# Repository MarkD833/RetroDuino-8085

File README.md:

# RetroDuino-8085

I've been toying with the idea of creating an 8085 based microprocessor board around the size of an Arduino UNO ever since I came across the [65uino](https://hackaday.io/project/190260-65uino) board on the hackaday website.

# Table of contents
* [The wish list](#the-basics-of-the-design)
  - [The Microprocessor](#the-microprocessor)
  - [ROM](#rom)
  - [RAM](#ram)
  - [Serial](#serial)
  - [I/O](#digital-input-output)
  - [ADC](#analogue-to-digital-converter)
* [Board Layout](#the-board-layout)
* [Assembly Instructions](#assembly-instructions)
* [The 16V8 GAL](#the-16v8-gal)
* [Pinout](#pinout)
* [Software](#software)
* [PCB Files](#the-board-design-files)
* [Known Errors](#known-errors)
* [History](#history)
## The basics of the design

I started off with some basics:
| Item | Notes |
| :---- | :---- |
| Microprocessor | an 8085 device but which one and what clock speed |
| ROM | At least 8K maybe 16K - but do I need that much?  |
| RAM | 32K would be good to aim for |
| Serial | 1 serial port but bit bang or hardware? |
| I/O | Bit programmable i/o |
| Analogue In | A multi channel ADC if there's room |
| LEDs | At least 1 user LED |

Oh, and one other requirement - no surface mount chips or hard to solder parts!

That's quite a lot to cram into the footprint on an Arduino UNO!

After a lot of playing around with an Arduino UNO prototyping board and various chip sockets I came up with a basic design and layout.

## The Microprocessor

The 8085 is mostly seen in a 40-pin DIL package. That's a huge amount of real estate on a footprint the size of an Arduino UNO. I discovered that OKI Semiconductor manufactured an 80C85 in a 44-pin PLCC package (MSM80C85AHGS-2K). After a quick bit of digging I located the datasheet and also a source on ebay that was selling some of the chips as NOS (New Old Stock).

Additional board space is consumed as the 8085 has a multiplexed address and data bus. The lower 8-bits are shared between D0..D7 and A0..A7 and an 8-bit latch (74LS573) is used to capture A0..A7.

Another design challenge is that the 8085 interrupts (if I were to use them) are active high rather than active low! 

The 8085 is clocked from an 11.0592MHz crystal, which gives an actual clock of 5.5296MHz (the 8085 divides the crystal frequency by 2). I've yet to experiment to see the effects of a higher frequency even though I'm exceeding the manufacturers 10MHz clock by 10% already.

## ROM

There are quite a few ROM devices available in a PLCC package as well, but I decided to go with a Winbond W27C512 64K x 8 EEPROM in a 28-pin DIL package. There's plenty for sale on ebay too. The reason for going the DIL package route will become clear with the choice of RAM device.

## RAM

I couldn't find any suitable RAM devices in PLCC format so the project success was looking rather bleak. Then I discovered that there were some SRAM devices available in DIL packages that were only 0.3in wide (called Skinny-DIP if I recall correctly). I then got lucky and sourced some UMC UM61512AK 64K x 8 SRAMs in a skinny 32-pin DIL package.

The RAM chip could sit underneath the ROM chip and I would save a lot of board space.

## Serial

I thought about bit banging the serial port using the SID and SOD pins of the 8085 but decided to try and go with real hardware. Again board space was at a premium so the hunt was on for a small UART device. A lot of serial chips have a large number of pins dedicated to various handshaking signals as well as synchronous data transfer - although some devices allow repurposing of these signals as discrete inputs or outputs. They are all still quite large chips in either PLCC or 0.6in DIL packages.

I then discovered a Philips SCC2691 UART (SCC2691AC1N24) that was available in a 0.3in wide 24-pin DIL package. It had an internal baud rate generator and a single 16-bit timer/counter as well. 

## Digital Input Output

I really wanted the I/O chip to have pin programmable direction control. That ruled out the 8155 and 8255 chips. It took a lot of searching but I then discovered a Zilog Z85C36. It had 2x 8-bit bit programmable I/O ports as well as 3x 16-bit timer/counters. That would be perfect!

Except that it wasn't! In my v1.0 design, I couldn't get the Z85C36 to respond at all. I don't know quite what the issue was as I was sure that I was meeting the timing requirements - but clearly something wasn't right.

In order to salvage the situation, I changed the I/O chip to a WDC W65C22S device. The chip still gave me 2x 8-bit bit programmable I/O ports, but only 2x 16-bit timer/counters.

## Analogue to Digital Converter

If I could fit it in, then an a National Semiconductor ADC0844 might work out - it's a 4 channel ADC in a 20-pin DIL package. 

# The board layout

There was quite a bit of massaging to get everything to fit as I also used a GAL16V8 to handle address decoding and interrupt inversion. The result was a board slightly longer than an Arduino UNO (but the same width).

This is an annotated 3D view of the board generated by Kicad as it stands at v1.2.

The thick white lines on the silkscreen just to the right of the FTDI serial port connector and the ADC0844 chip show the outline of an actual Arduino UNO board.

# Assembly Instructions

Assembly of the board is pretty straightforward with a few things of note.

1. Solder all the small SMD resistors and capacitors first - especially on the top of the board as there is very little room once the IC sockets are fitted.
2. Solder the microprocessor crystal and Reset device before fitting the 44-pin PLCC sockets otherwise you may find that the crystal will not fit down between the 44-pin PLCC sockets. 
3. Depending on the particular DIL socket(s) used for the SCC2691 UART, you may need to remove some of the plastic from the socket so that the 3.6864MHz crystal fits. I used 2 turned-pin sockets, an 8-pin and a 16-pin, to create the 24-pin socket needed. I found that the turned pin socket was less bulky than a regular socket.
4. The 28-pin DIL socket for the W27C512 ROM needs modifying. As the RAM chip will be sitting underneath the ROM chip, I removed the 3 pieces of plastic between the 2 rows of pins - effectively creating two separate 14-pin SIL sockets.
5. Lastly, solder the 4 SIL sockets. These pretty much seal off the top of the board for any further access with a soldering iron, so make sure that the board works before fitting thse. 

This is a photo of the RetroDuino-8085 board showing the location of the 3.6864MHz UART crystal and the modified 28-pin DIL socket.

# The 16V8 GAL

There's so little space on this board that a GAL seemed the logical choice to handle the usual discrete logic. The GAL does address and i/o decoding as follows:
* Memory space
  * 0x0000 - 0x3FFF selects the ROM
  * 0x4000 - 0xFFFF selets the RAM
* I/O space
  * 0x00 - 0x3F selects the SCC2692 UART
  * 0x40 - 0x7F selects the W65C22S digital i/o chip
  * 0x80 - 0xBF selects the ADC0844 ADC chip
 
In addition, the GAL inverts the SCC2692 and W65C22S interrupt signals.

Finally, the GAL has the ability to completely switch out the ROM to give access to the full 64K or RAM. The 8085 SOD pin is used to control this feature.

The GAL files are in the code folder.

# Pinout
Below is an image of the pinout I'm using - laid out in a similar way to the Arduino pinout diagrams found on the web. Note that the I2C and SPI signals will hopefully be generated by a software implementation of a hardware interface. 

# Software

Please see the readme in the Code folder for more details on the software.

# The board design files

The board folder holds the gerber files that were sent to JLCPCB to make the board. It's a 4 layer board but small enough to get it made very cheaply.

The design was done using Kicad 7.0. I'm not sure exactly which files I need to share for the schematic and board layout so I've put the .kicad_pro, .kicad_sch & .kicad_sch files into the board folder. There's also the BOM as a CSV file showing the components used.

# Known errors

Yep, there are errors with v1.2. So far:
* LED D2 wrong way round
* LED D3 wrong way round

# History
* v1.2
  * Used ALE to clock the GAL rather than SYSCLK.
  * Removed the CompactFlash socket and associated passives.
  * Used 8085 SOD discrete to switch out the ROM.
  * Addition of 2nd user LED.
  * Repositioning of the FTDI connector.
* v1.1 
  * Updated design using the W65C22 PIA chip.
* v1.0
  * Initial design using the Z85C36 CIO chip.

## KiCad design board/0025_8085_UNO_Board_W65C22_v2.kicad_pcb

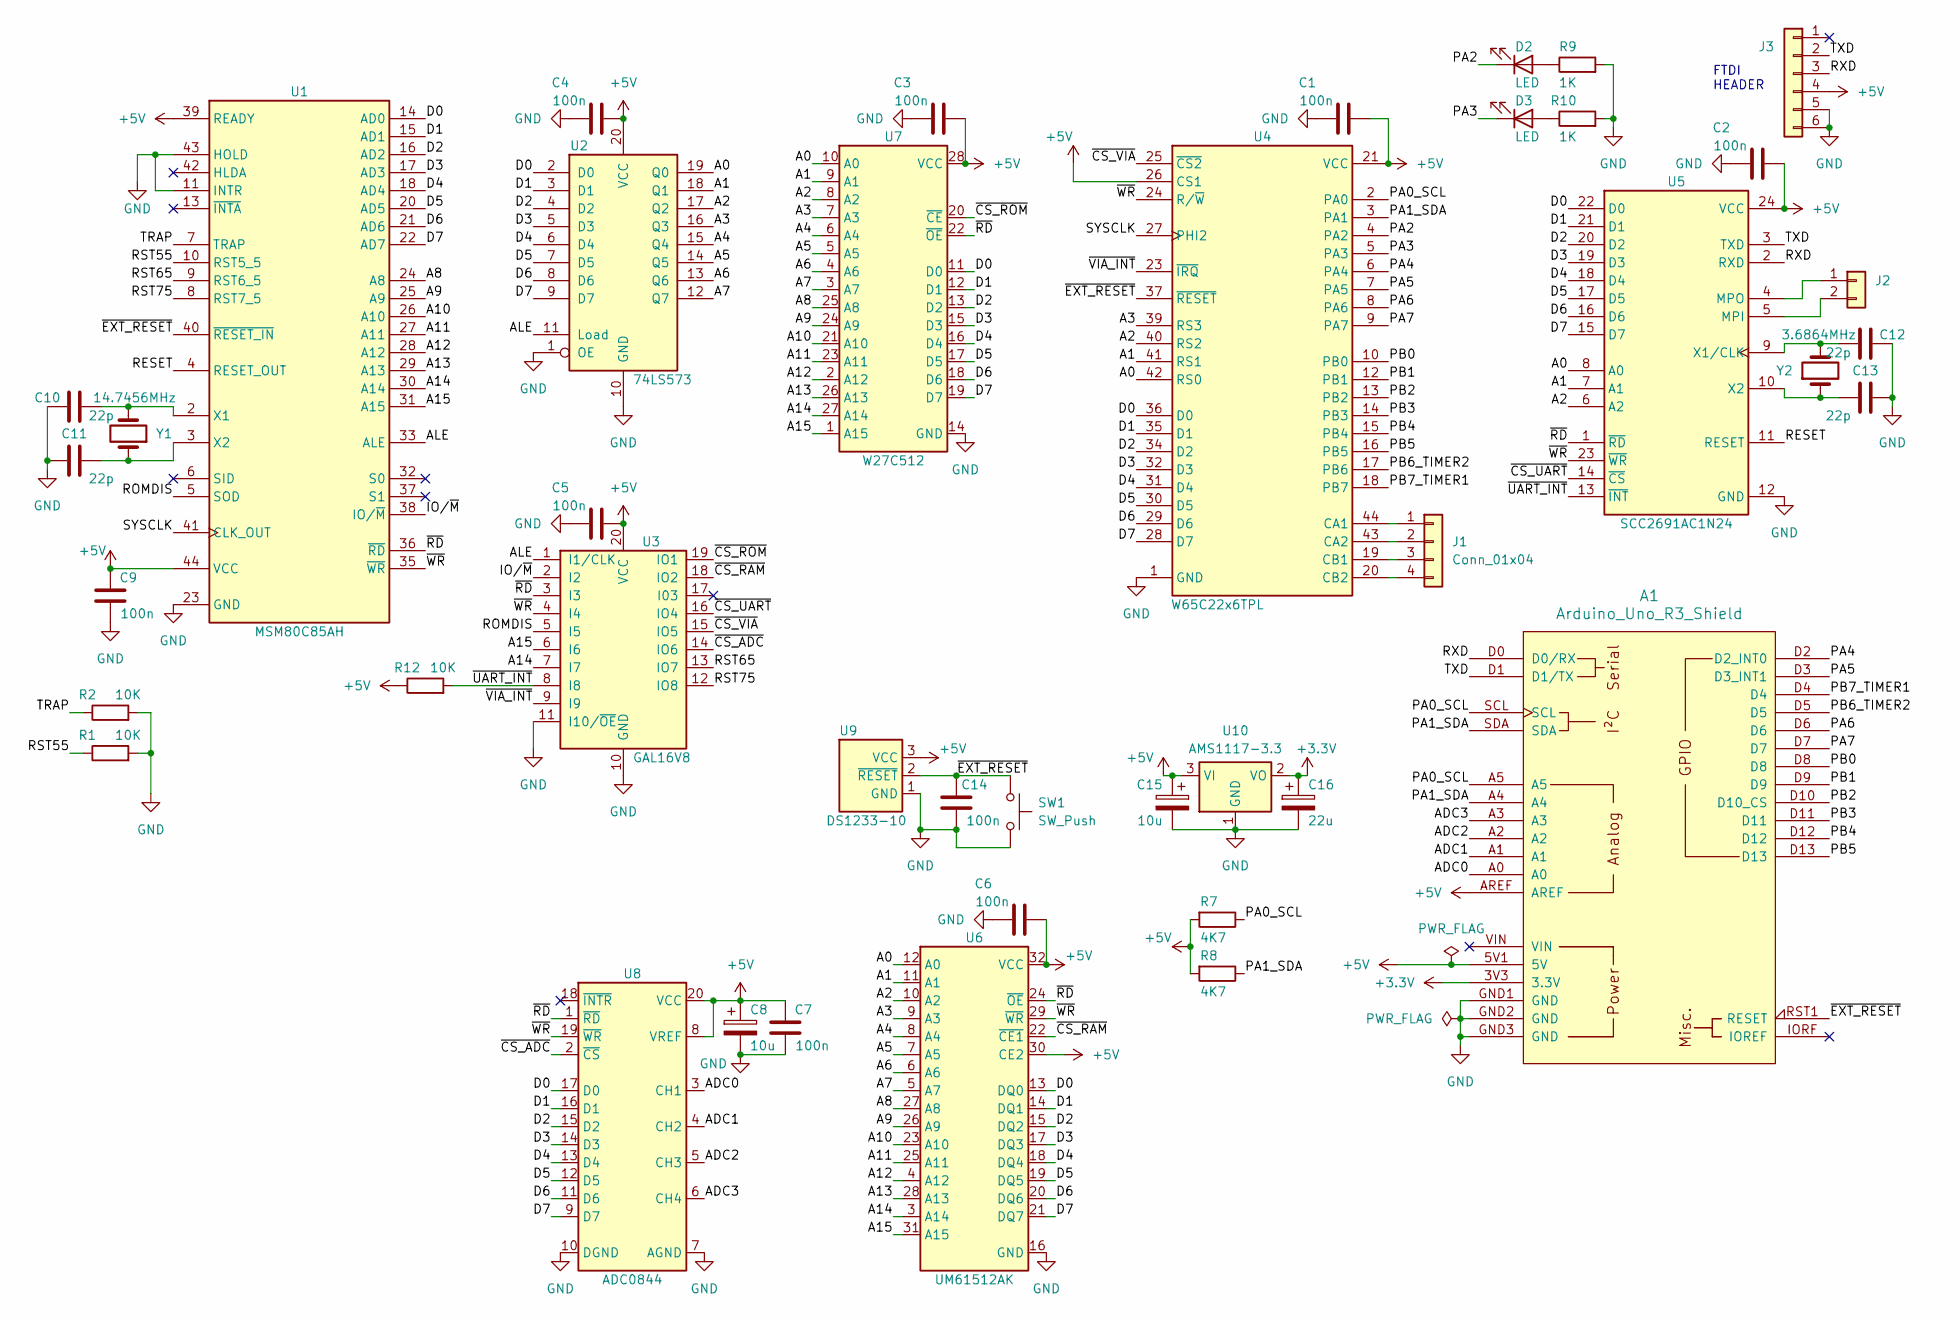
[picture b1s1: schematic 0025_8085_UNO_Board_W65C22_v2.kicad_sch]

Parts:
A1: Arduino_Uno_R3_Shield; Arduino_Uno_8085_Base_1
C1, C2, C3, C4, C5, C6, C7, C9, C14: 100n; C_0603_1608Metric_Pad1.08x0.95mm_HandSolder
C8: 10u; CP_EIA-3216-18_Kemet-A
C10, C11, C12, C13: 22p; C_0603_1608Metric_Pad1.08x0.95mm_HandSolder
C15: 10u; CP_EIA-3216-18_Kemet-A_Pad1.58x1.35mm_HandSolder
C16: 22u; CP_EIA-6032-28_Kemet-C
D2, D3: LED; LED_0805_2012Metric_Pad1.15x1.40mm_HandSolder
J1: Conn_01x04; PinHeader_1x04_P2.54mm_Vertical
J2: PinHeader_1x02_P2.54mm_Vertical
J3: PinHeader_1x06_P2.54mm_Vertical
R1, R2, R12: 10K; R_0805_2012Metric_Pad1.20x1.40mm_HandSolder
R7, R8: 4K7; R_0805_2012Metric_Pad1.20x1.40mm_HandSolder
R9, R10: 1K; R_0805_2012Metric_Pad1.20x1.40mm_HandSolder
SW1: SW_Push; TACTILE_SWITCH_SMD_6.0X3.5MM
U1: MSM80C85AH; PLCC-44_THT-Socket
U2: 74LS573; DIP-20_W7.62mm
U3: GAL16V8; DIP-20_W7.62mm
U4: W65C22x6TPL; PLCC-44_THT-Socket
U5: SCC2691AC1N24; DIP-24_W7.62mm
U6: UM61512AK; DIP-32_W7.62mm
U7: W27C512; DIP-28_W15.24mm
U8: ADC0844; DIP-20_W7.62mm
U9: DS1233-10; TO-92L_Inline
U10: AMS1117-3.3; SOT-223-3_TabPin2
Y1: 14.7456MHz; Crystal_HC49-U_Vertical
Y2: 3.6864MHz; Crystal_HC49-U_Vertical

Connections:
+3.3V: A1.3V3 (3.3V), C16.1, U10.2 (VO)
+5V: A1.5V1 (5V), A1.AREF, C1.2, C2.2, C3.2, C4.2, C5.2, C6.2, C7.1, C8.1, C9.1, C15.1, J3.4, R7.2, R8.2, R12.1, U1.39 (READY), U1.44 (VCC), U2.20 (VCC), U3.20 (VCC), U4.21 (VCC), U4.26 (CS1), U5.24 (VCC), U6.30 (CE2), U6.32 (VCC), U7.28 (VCC), U8.8 (VREF), U8.20 (VCC), U9.3 (VCC), U10.3 (VI)
/A0: U2.19 (Q0), U4.42 (RS0), U5.8 (A0), U6.12 (A0), U7.10 (A0)
/A1: U2.18 (Q1), U4.41 (RS1), U5.7 (A1), U6.11 (A1), U7.9 (A1)
/A2: U2.17 (Q2), U4.40 (RS2), U5.6 (A2), U6.10 (A2), U7.8 (A2)
/A3: U2.16 (Q3), U4.39 (RS3), U6.9 (A3), U7.7 (A3)
/A4: U2.15 (Q4), U6.8 (A4), U7.6 (A4)
/A5: U2.14 (Q5), U6.7 (A5), U7.5 (A5)
/A6: U2.13 (Q6), U6.6 (A6), U7.4 (A6)
/A7: U2.12 (Q7), U6.5 (A7), U7.3 (A7)
/A8: U1.24 (A8), U6.27 (A8), U7.25 (A8)
/A9: U1.25 (A9), U6.26 (A9), U7.24 (A9)
/A10: U1.26 (A10), U6.23 (A10), U7.21 (A10)
/A11: U1.27 (A11), U6.25 (A11), U7.23 (A11)
/A12: U1.28 (A12), U6.4 (A12), U7.2 (A12)
/A13: U1.29 (A13), U6.28 (A13), U7.26 (A13)
/A14: U1.30 (A14), U3.7 (I7), U6.3 (A14), U7.27 (A14)
/A15: U1.31 (A15), U3.6 (I6), U6.31 (A15), U7.1 (A15)
/ADC0: A1.A0, U8.3 (CH1)
/ADC1: A1.A1, U8.4 (CH2)
/ADC2: A1.A2, U8.5 (CH3)
/ADC3: A1.A3, U8.6 (CH4)
/ALE: U1.33 (ALE), U2.11 (Load), U3.1 (I1/CLK)
/D0: U1.14 (AD0), U2.2 (D0), U4.36 (D0), U5.22 (D0), U6.13 (DQ0), U7.11 (D0), U8.17 (D0)
/D1: U1.15 (AD1), U2.3 (D1), U4.35 (D1), U5.21 (D1), U6.14 (DQ1), U7.12 (D1), U8.16 (D1)
/D2: U1.16 (AD2), U2.4 (D2), U4.34 (D2), U5.20 (D2), U6.15 (DQ2), U7.13 (D2), U8.15 (D2)
/D3: U1.17 (AD3), U2.5 (D3), U4.32 (D3), U5.19 (D3), U6.17 (DQ3), U7.15 (D3), U8.14 (D3)
/D4: U1.18 (AD4), U2.6 (D4), U4.31 (D4), U5.18 (D4), U6.18 (DQ4), U7.16 (D4), U8.13 (D4)
/D5: U1.20 (AD5), U2.7 (D5), U4.30 (D5), U5.17 (D5), U6.19 (DQ5), U7.17 (D5), U8.12 (D5)
/D6: U1.21 (AD6), U2.8 (D6), U4.29 (D6), U5.16 (D6), U6.20 (DQ6), U7.18 (D6), U8.11 (D6)
/D7: U1.22 (AD7), U2.9 (D7), U4.28 (D7), U5.15 (D7), U6.21 (DQ7), U7.19 (D7), U8.9 (D7)
/IO/~M: U1.38 (IO/~M), U3.2 (I2)
/PA0_SCL: A1.A5, A1.SCL, R7.1, U4.2 (PA0)
/PA1_SDA: A1.A4, A1.SDA, R8.1, U4.3 (PA1)
/PA2: D2.1 (K), U4.4 (PA2)
/PA3: D3.1 (K), U4.5 (PA3)
/PA4: A1.D2 (D2_INT0), U4.6 (PA4)
/PA5: A1.D3 (D3_INT1), U4.7 (PA5)
/PA6: A1.D6, U4.8 (PA6)
/PA7: A1.D7, U4.9 (PA7)
/PB0: A1.D8, U4.10 (PB0)
/PB1: A1.D9, U4.12 (PB1)
/PB2: A1.D10 (D10_CS), U4.13 (PB2)
/PB3: A1.D11, U4.14 (PB3)
/PB4: A1.D12, U4.15 (PB4)
/PB5: A1.D13, U4.16 (PB5)
/PB6_TIMER2: A1.D5, U4.17 (PB6)
/PB7_TIMER1: A1.D4, U4.18 (PB7)
/RESET: U1.4 (RESET_OUT), U5.11 (RESET)
/ROMDIS: U1.5 (SOD), U3.5 (I5)
/RST55: R1.1, U1.10 (RST5_5)
/RST65: U1.9 (RST6_5), U3.13 (IO7)
/RST75: U1.8 (RST7_5), U3.12 (IO8)
/RXD: A1.D0 (D0/RX), J3.3, U5.2 (RXD)
/SYSCLK: U1.41 (CLK_OUT), U4.27 (PHI2)
/TRAP: R2.1, U1.7 (TRAP)
/TXD: A1.D1 (D1/TX), J3.2, U5.3 (TXD)
/~CS_ADC: U3.14 (IO6), U8.2 (~CS)
/~CS_RAM: U3.18 (IO2), U6.22 (~CE1)
/~CS_ROM: U3.19 (IO1), U7.20 (~CE)
/~CS_UART: U3.16 (IO4), U5.14 (~CS)
/~CS_VIA: U3.15 (IO5), U4.25 (~CS2)
/~EXT_RESET: A1.RST1 (RESET), C14.1, SW1.1, U1.40 (~RESET_IN), U4.37 (~RESET), U9.2 (~RESET)
/~RD: U1.36 (~RD), U3.3 (I3), U5.1 (~RD), U6.24 (~OE), U7.22 (~OE), U8.1 (~RD)
/~UART_INT: R12.2, U3.8 (I8), U5.13 (~INT)
/~VIA_INT: U3.9 (I9), U4.23 (~IRQ)
/~WR: U1.35 (~WR), U3.4 (I4), U4.24 (R/~W), U5.23 (~WR), U6.29 (~WR), U8.19 (~WR)
GND: A1.GND1 (GND), A1.GND2 (GND), A1.GND3 (GND), C1.1, C2.1, C3.1, C4.1, C5.1, C6.1, C7.2, C8.2, C9.2, C10.1, C11.2, C12.1, C13.2, C14.2, C15.2, C16.2, J3.5, J3.6, R1.2, R2.2, R9.2, R10.2, SW1.2, U1.11 (INTR), U1.23 (GND), U1.43 (HOLD), U2.1 (OE), U2.10 (GND), U3.10 (GND), U3.11 (I10/~OE), U4.1 (GND), U5.12 (GND), U6.16 (GND), U7.14 (GND), U8.7 (AGND), U8.10 (DGND), U9.1 (GND), U10.1 (GND)
unnamed: D2.2 (A), R9.1
unnamed: D3.2 (A), R10.1
unnamed: J1.1, U4.44 (CA1)
unnamed: J1.2, U4.43 (CA2)
unnamed: J1.3, U4.19 (CB1)
unnamed: J1.4, U4.20 (CB2)
unnamed: J2.1, U5.4 (MPO)
unnamed: J2.2, U5.5 (MPI)
unnamed: C10.2, U1.2 (X1), Y1.2
unnamed: C11.1, U1.3 (X2), Y1.1
unnamed: C12.2, U5.9 (X1/CLK), Y2.2
unnamed: C13.1, U5.10 (X2), Y2.1

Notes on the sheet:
FTDI HEADER

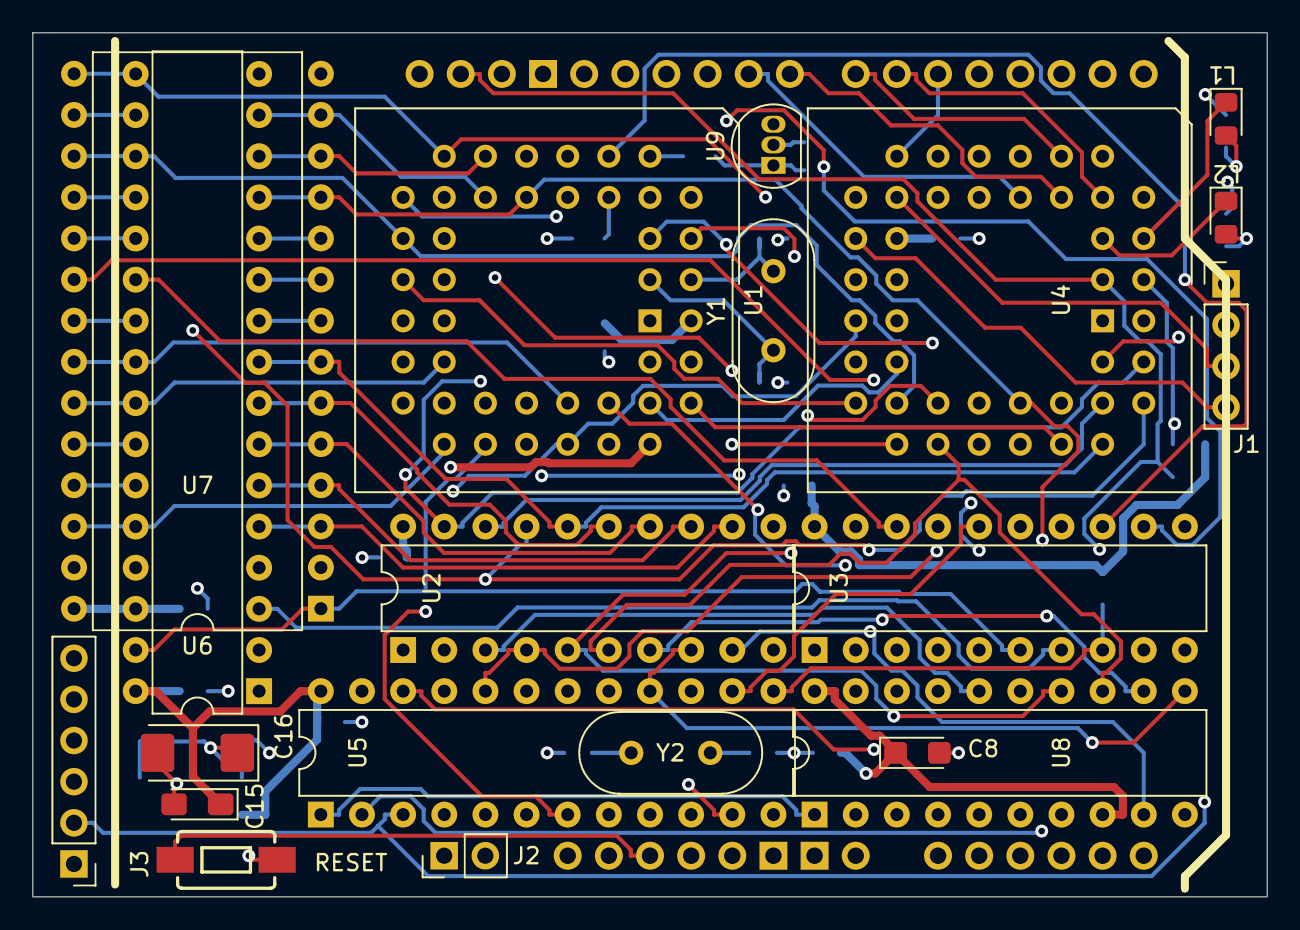
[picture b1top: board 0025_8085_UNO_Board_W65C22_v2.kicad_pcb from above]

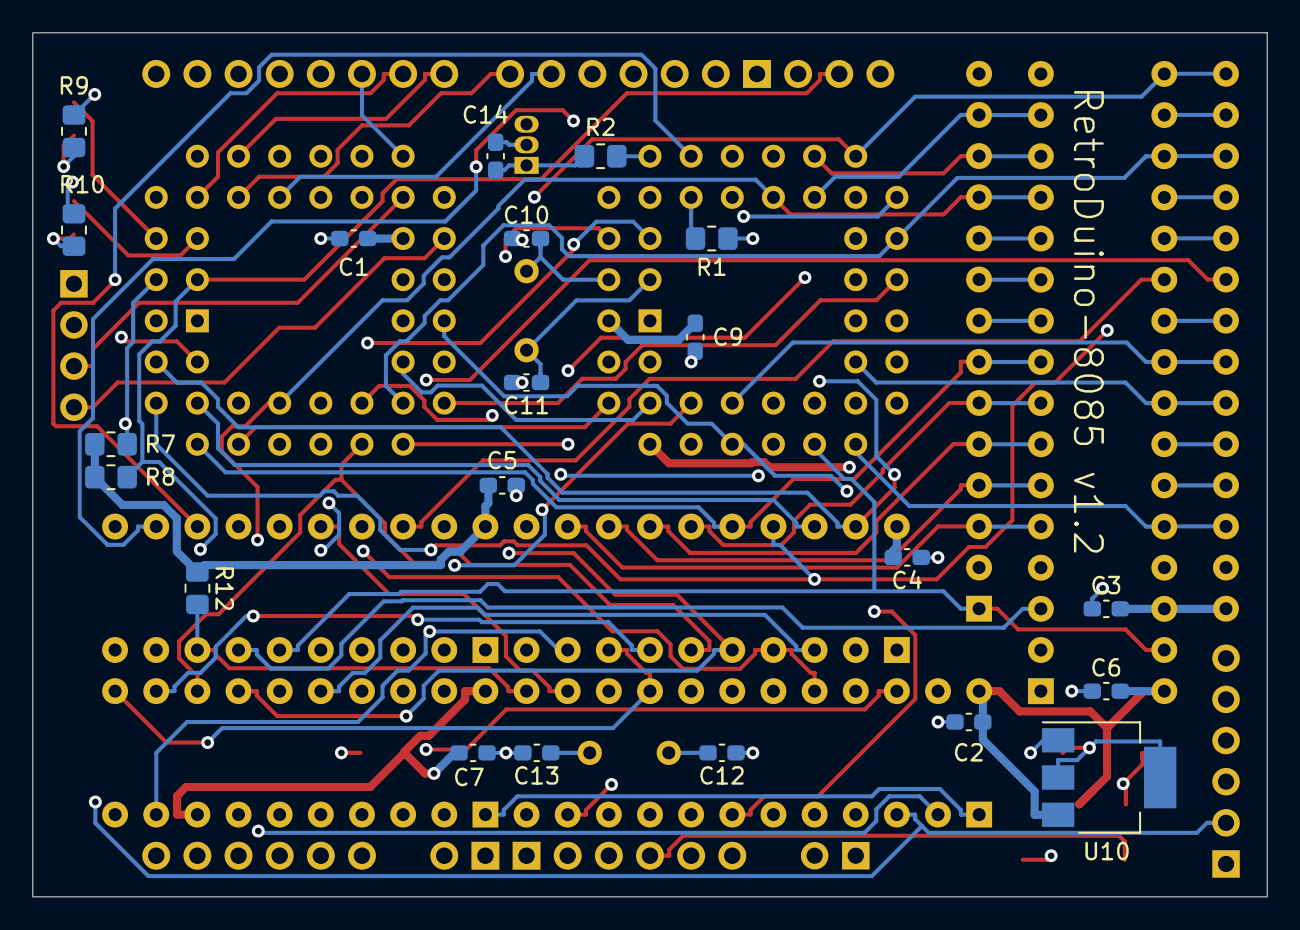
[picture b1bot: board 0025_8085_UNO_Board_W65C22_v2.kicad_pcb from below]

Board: 4 copper layers, 76.2 x 53.3 mm, 42 parts (21 on the bottom side), 80 nets.

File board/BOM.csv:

"Source:","D:\KiCad_Projects\0025_8085_UNO_Board_W65C22_v2\0025_8085_UNO_Board_W65C22_v2.kicad_sch"
"Date:","25/01/2024 17:21:43"
"Tool:","Eeschema 7.0.5"
"Generator:","D:\Program Files\KiCad\7.0\bin\scripting\plugins/bom_csv_grouped_by_value.py"
"Component Count:","42"

"Collated Components:"

"Item","Qty","Reference(s)","Value","LibPart","Footprint","Datasheet","DNP"
"1","1","A1","Arduino_Uno_R3_Shield","MyLibrary2023:Arduino_Uno_R3_Shield","MyLibrary2023:Arduino_Uno_8085_Base_1","",""
"2","9","C1, C2, C3, C4, C5, C6, C7, C9, C14","100n","Device:C","Capacitor_SMD:C_0603_1608Metric_Pad1.08x0.95mm_HandSolder","~",""
"3","1","C8","10u","Device:C_Polarized","Capacitor_Tantalum_SMD:CP_EIA-3216-18_Kemet-A","~",""
"4","4","C10, C11, C12, C13","22p","Device:C","Capacitor_SMD:C_0603_1608Metric_Pad1.08x0.95mm_HandSolder","~",""
"5","1","C15","10u","Device:C_Polarized","Capacitor_Tantalum_SMD:CP_EIA-3216-18_Kemet-A_Pad1.58x1.35mm_HandSolder","~",""
"6","1","C16","22u","Device:C_Polarized","Capacitor_Tantalum_SMD:CP_EIA-6032-28_Kemet-C","~",""
"7","2","D2, D3","LED","Device:LED","LED_SMD:LED_0805_2012Metric_Pad1.15x1.40mm_HandSolder","~",""
"8","1","J1","Conn_01x04","Connector_Generic:Conn_01x04","Connector_PinHeader_2.54mm:PinHeader_1x04_P2.54mm_Vertical","~",""
"9","1","J2","~","Connector_Generic:Conn_01x02","Connector_PinHeader_2.54mm:PinHeader_1x02_P2.54mm_Vertical","~",""
"10","1","J3","~","Connector_Generic:Conn_01x06","Connector_PinHeader_2.54mm:PinHeader_1x06_P2.54mm_Vertical","~",""
"11","3","R1, R2, R12","10K","Device:R","Resistor_SMD:R_0805_2012Metric_Pad1.20x1.40mm_HandSolder","~",""
"12","2","R7, R8","4K7","Device:R","Resistor_SMD:R_0805_2012Metric_Pad1.20x1.40mm_HandSolder","~",""
"13","2","R9, R10","1K","Device:R","Resistor_SMD:R_0805_2012Metric_Pad1.20x1.40mm_HandSolder","~",""
"14","1","SW1","SW_Push","Switch:SW_Push","MyLibrary2023:TACTILE_SWITCH_SMD_6.0X3.5MM","~",""
"15","1","U1","MSM80C85AH","MyLibrary2023:MSM80C85AH","Package_LCC:PLCC-44_THT-Socket","",""
"16","1","U2","74LS573","74xx:74LS573","Package_DIP:DIP-20_W7.62mm","74xx/74hc573.pdf",""
"17","1","U3","GAL16V8","Logic_Programmable:GAL16V8","Package_DIP:DIP-20_W7.62mm","",""
"18","1","U4","W65C22x6TPL","MyLibrary2023:W65C22x6TPL","Package_LCC:PLCC-44_THT-Socket","",""
"19","1","U5","SCC2691AC1N24","MyLibrary2023:SCC2691AC1N24","Package_DIP:DIP-24_W7.62mm","",""
"20","1","U6","UM61512AK","MyLibrary2023:UM61512AK","Package_DIP:DIP-32_W7.62mm","",""
"21","1","U7","W27C512","MyLibrary2023:W27C512","Package_DIP:DIP-28_W15.24mm","",""
"22","1","U8","ADC0844","MyLibrary2023:ADC0844","Package_DIP:DIP-20_W7.62mm","",""
"23","1","U9","DS1233-10","MyLibrary2023:DS1233","Package_TO_SOT_THT:TO-92L_Inline","",""
"24","1","U10","AMS1117-3.3","Regulator_Linear:AMS1117-3.3","Package_TO_SOT_SMD:SOT-223-3_TabPin2","http://www.advanced-monolithic.com/pdf/ds1117.pdf",""
"25","1","Y1","11.0592MHz","Device:Crystal","Crystal:Crystal_HC49-U_Vertical","~",""
"26","1","Y2","3.6864MHz","Device:Crystal","Crystal:Crystal_HC49-U_Vertical","~",""

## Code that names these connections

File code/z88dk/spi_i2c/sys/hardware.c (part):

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*******************************************************************************
* SPI - Software emulation
* SPI signals are configured to match those of the Arduino UNO such that:
*  MOSI = Arduino UNO PB3 = RetroDuino 8085 VIA PB3
*  MISO = Arduino UNO PB4 = RetroDuino 8085 VIA PB4
*  SCK  = Arduino UNO PB5 = RetroDuino 8085 VIA PB5
******************************************************************************/


/******************************************************************************
* spiSetup - sets up the port pins associated with software SPI
*            PB5 (out) = SCK, PB4 (in) = MISO & PB3 (out) = MOSI
******************************************************************************/
void spiSetup( void )
{
	/* Set PB4 as an input and PB3 & PB5 as outputs */
	VIA_DDRB = ( VIA_DDRB & 0xEF ) | 0x28;
	
	/* Set SCK low */
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*******************************************************************************
* I2C - Software emulation
* I2C signals are configured to match those of the Arduino UNO such that:
*  SCL = Arduino UNO PC5 = RetroDuino 8085 VIA PA0
*  SDA = Arduino UNO PC4 = RetroDuino 8085 VIA PA1
******************************************************************************/

/******************************************************************************
* i2cSetup - sets up the port pins associated with software I2C
*            PA0 (out) = SCL & PA1 (out) = SDA
******************************************************************************/
void i2cSetup( void )
{
	/* Set PA0 & PA1 as outputs */
	VIA_DDRA = VIA_DDRA | 0x03;
	
	/* Set SCL & SDA HIGH */
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
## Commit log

2024-01-18 more description and images
2024-01-19 added images
2024-01-19 Added GAL details
2024-01-19 update images
2024-01-19 added history
2024-01-20 Added MON85 + GAL code
2024-01-25 Added PCB information
    PCB details have been added along with amendments to the README file.
2024-01-25 minor documentation update
2024-01-26 update documentation
2024-01-26 more documenation
2024-01-26 added LED flasher test program
2024-01-27 added pinout diagram
2024-01-27 correction for SPI & I2C
2024-01-28 added second LEDTest code
    New LEDTest code that demonstrates how to run completely in RAM with MON85 switched out.
2024-01-28 Updated MON85 & LEDTest2
    MON85 now includes the ROM disable and JMP 0x0000 instructions. LEDTest2 changed to remove this code as it's now in MON85.
2024-01-31 added z88dk hello example
2024-01-31 corrections to text
2024-01-31 silly mistake
2024-02-16 Added assembly step
2024-02-27 added SPI, I2C & sys tick functionality
